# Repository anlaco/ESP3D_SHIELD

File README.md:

# ESP3D_SHIELD
placa para convertir el esp32 devkit v1 en una placa controladora de impresora 3d

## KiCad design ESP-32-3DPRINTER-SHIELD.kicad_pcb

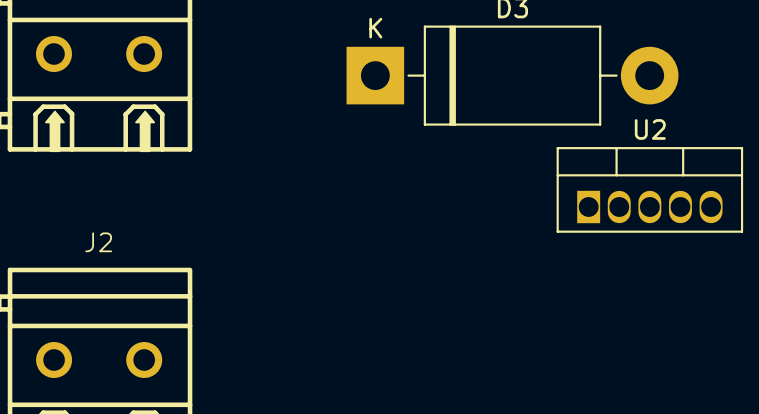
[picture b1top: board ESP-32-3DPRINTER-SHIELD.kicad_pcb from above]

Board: 2 copper layers, 4 parts (0 on the bottom side), 4 nets, no tracks yet.

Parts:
D3: 1N5821; D_DO-201AD_P15.24mm_Horizontal
J1, J2: WJ128V-5.0-2P; CONN-TH_2P-P5.00_WJ128V-5.0-2P
U2: LM2596T; TO-220-5_Vertical

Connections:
+5V: J2.1, U2.4 (FeedBack)
+24V: J1.1, U2.1 (Vin)
GND: D3.2 (A), J1.2, J2.2, U2.3 (GND), U2.5 (~ON/OFF)
unnamed: D3.1 (K), U2.2 (Output)

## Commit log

2025-04-10 añadido diodo de proteccion y conector de salida de 24V
